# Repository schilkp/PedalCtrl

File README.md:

# PedalCtrl
Philipp Schilk 2020

https://github.com/TheSchilk/PedalCtrl

A very simple, PIC12F1572-based, footpedal-controlled, relay 250V Mains switch.

## Mandatory Warning

Please don't work with mains-connected circuits unless you know what you are doing.

## Status

Waiting for PCB prototype to develop Firmware.

## Details

Allows mains-powered devices to be quickly powered on and off using a footswitch.
Both Line and Neutral are switched.

Pressing the pedal once enables the device and starts an automatic timer controlled
by the potentiometer. Once that timer runs out, or the pedal is pressed again, the 
device will switch back off.

Quickly pressing the pedal twice causes the device to stay permanently powered on until
the pedal is pressed again.

## Production Files
Please see Github 'Releases' for Schematic, Gerbers, Interactive BOM usw.

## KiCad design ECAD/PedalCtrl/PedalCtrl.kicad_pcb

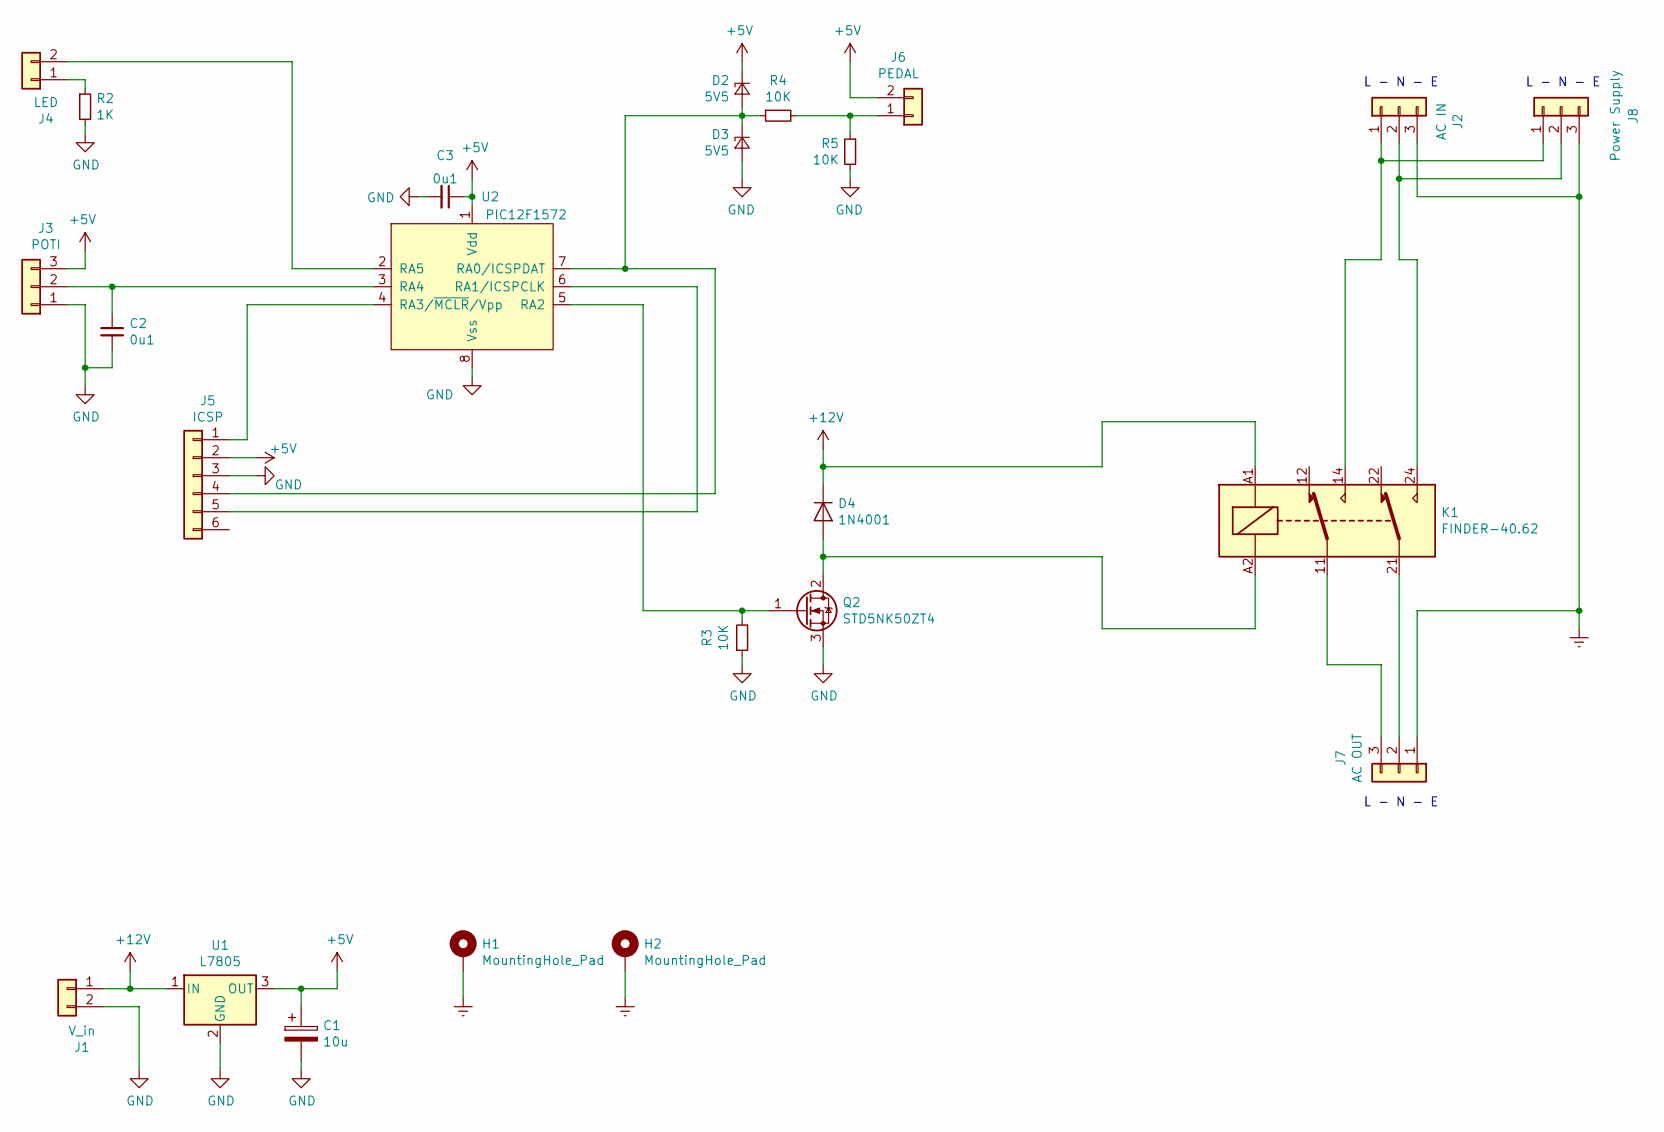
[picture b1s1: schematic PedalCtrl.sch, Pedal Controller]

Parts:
C1: 10u; CP_Elec_6.3x7.7
C2, C3: 0u1; C_0603_1608Metric
D2, D3: 5V5; D_SOD-123
D4: 1N4001; D_SOD-123F
H1, H2: MountingHole_Pad; MountingHole_3.2mm_M3_Pad_Via
J1: V_in; TerminalBlock_Phoenix_MKDS-1,5-2_1x02_P5.00mm_Horizontal
J2: AC IN; TerminalBlock_Phoenix_MKDS-1,5-3_1x03_P5.00mm_Horizontal
J3: POTI; PinHeader_1x03_P2.54mm_Vertical
J4: LED; PinHeader_1x02_P2.54mm_Vertical
J5: ICSP; PinHeader_1x06_P2.54mm_Vertical
J6: PEDAL; PinHeader_1x02_P2.54mm_Vertical
J7: AC OUT; TerminalBlock_Phoenix_MKDS-1,5-3_1x03_P5.00mm_Horizontal
J8: Power Supply; TerminalBlock_Phoenix_MKDS-1,5-3_1x03_P5.00mm_Horizontal
K1: FINDER-40.62; Relay_DPDT_Finder_40.52
Q2: STD5NK50ZT4; TO-252-2
R2: 1K; R_0603_1608Metric
R3, R4, R5: 10K; R_0603_1608Metric
U1: L7805; TO-252-2
U2: PIC12F1572; SOIC-8_3.9x4.9mm_P1.27mm

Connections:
+5V: C1.1, C3.1, D2.1 (K), J3.3, J5.2, J6.2, U1.3 (OUT), U2.1 (Vdd)
+12V: D4.1 (K), J1.1, K1.A1, U1.1 (IN)
Earth: H1.1, H2.1, J2.3, J7.1, J8.3
GND: C1.2, C2.2, C3.2, D3.2 (A), J1.2, J3.1, J5.3, Q2.3 (S), R2.2, R3.1, R5.2, U1.2 (GND), U2.8 (Vss)
unnamed: C2.1, J3.2, U2.3 (RA4)
unnamed: D2.2 (A), D3.1 (K), J5.4, R4.1, U2.7 (RA0/ICSPDAT)
unnamed: D4.2 (A), K1.A2, Q2.2 (D)
unnamed: J2.1, J8.1, K1.14
unnamed: J2.2, J8.2, K1.24
unnamed: J4.1, R2.1
unnamed: J4.2, U2.2 (RA5)
unnamed: J5.1, U2.4 (RA3/~MCLR~/Vpp)
unnamed: J5.5, U2.6 (RA1/ICSPCLK)
unnamed: J6.1, R4.2, R5.1
unnamed: J7.2, K1.21
unnamed: J7.3, K1.11
unnamed: Q2.1 (G), R3.2, U2.5 (RA2)

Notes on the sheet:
L - N - E

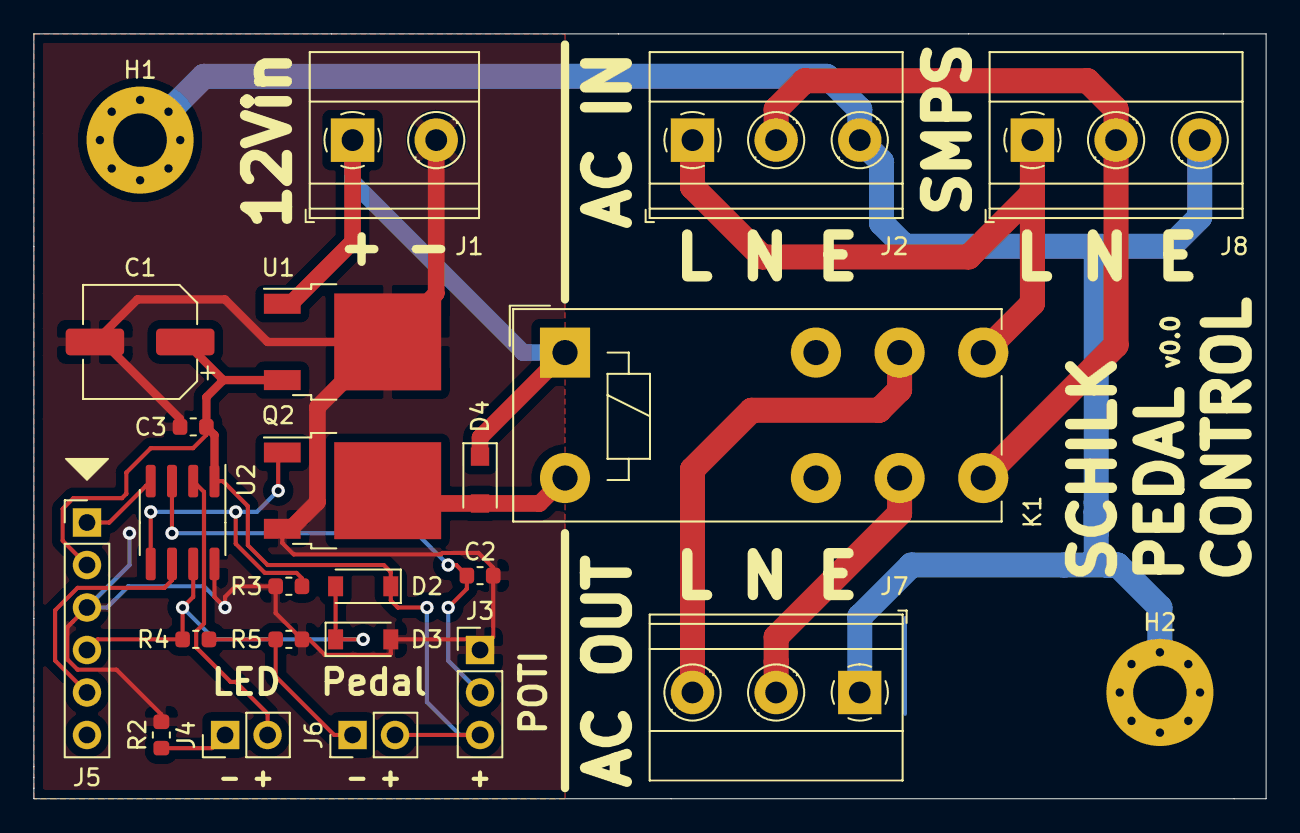
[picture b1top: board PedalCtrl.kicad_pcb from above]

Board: 2 copper layers, 73.7 x 45.7 mm, 24 parts (0 on the bottom side), 17 nets.

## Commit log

2020-09-19 v0.0
2020-09-20 Doc Update
2020-09-20 Added Render to README.md
2020-09-20 Added Status
2020-09-20 Added MPLAB gitignore
2020-09-20 Added Skeleton from VacTool
2020-09-20 Moved KiCad .gitignore
2020-09-25 First draft firmware
2020-09-26 Finished firmware. Better UI timings & LED blinks
2021-05-24 Added .gitattributes
